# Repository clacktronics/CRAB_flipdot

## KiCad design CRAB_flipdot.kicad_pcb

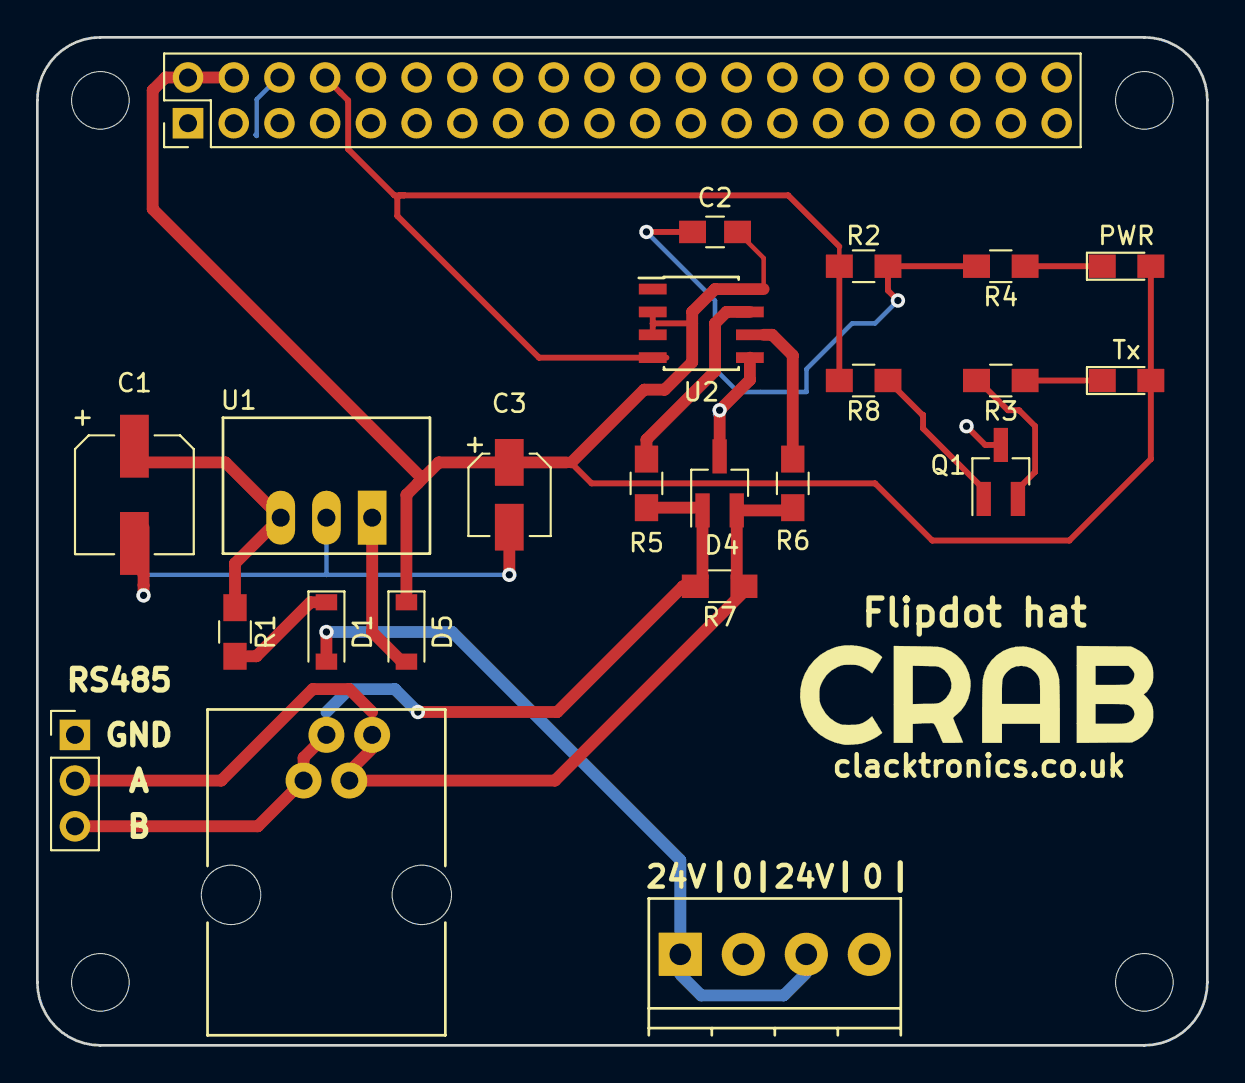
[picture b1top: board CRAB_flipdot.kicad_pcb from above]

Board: 2 copper layers, 65.0 x 56.0 mm, 23 parts (0 on the bottom side), 15 nets.

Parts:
C1: 22u; CP_Elec_6.3x4.5
C2: 100n; C_0805_HandSoldering
C3: 10u; CP_Elec_4x4.5
D1, D5: D_Schottky; D_SOD-123
D4: CDSOT23-SM712; SOT-23_Handsoldering
H1: RaspberryPi-cap_template; Pin_Header_Straight_2x20_Pitch2.54mm
J1: Screw_Terminal_01x04; TerminalBlock_Phoenix_PT-3.5mm_4pol
J2: Conn_01x03; Pin_Header_Straight_1x03_Pitch2.54mm
J3: RJ11; Molex RJ11 95501-2641
PWR: LED; LED_0805_HandSoldering
Q1: Q_NMOS_GDS; SOT-23_Handsoldering
R1: 10; R_0805_HandSoldering
R2: 47k; R_0805_HandSoldering
R3, R4: 1k; R_0805_HandSoldering
R5, R6: 10R; R_0805_HandSoldering
R7: 120R; R_0805_HandSoldering
R8: 100R; R_0805_HandSoldering
Tx: LED; LED_0805_HandSoldering
U1: R-785.0-1.0
U2: sn65hvd72d; SOIC-8_3.9x4.9mm_Pitch1.27mm

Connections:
+5V: C2.1, C3.1, D5.1, H1.2, H1.4, PWR.2, Tx.2, U2.2, U2.3, U2.8
A_OUT: D4.2, J2.2, J3.3, J3.4, R6.1, R7.1
B_OUT: D4.1, J2.3, J3.1, J3.2, R5.1, R7.2
GND: C1.2, C2.2, C3.2, D4.3, H1.6, J1.2, J1.4, J2.1, Q1.3, R2.2, R4.2, U1.2, U2.5
unnamed: C1.1, R1.1, U1.3
unnamed: D1.1, R1.2
unnamed: D1.2, J1.1, J1.3
unnamed: R3.1, Tx.1
unnamed: PWR.1, R4.1
unnamed: D5.2, U1.1
unnamed: H1.8, R2.1, R8.2, U2.4
unnamed: Q1.1, R8.1
unnamed: Q1.2, R3.2
unnamed: R5.2, U2.7
unnamed: R6.2, U2.6

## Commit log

2018-07-23 Started schematic
2018-08-23 Board added
2018-08-29 Prototype ready
